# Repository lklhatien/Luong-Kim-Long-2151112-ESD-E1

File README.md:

# Luong-Kim-Long-2151112-ESD-E1

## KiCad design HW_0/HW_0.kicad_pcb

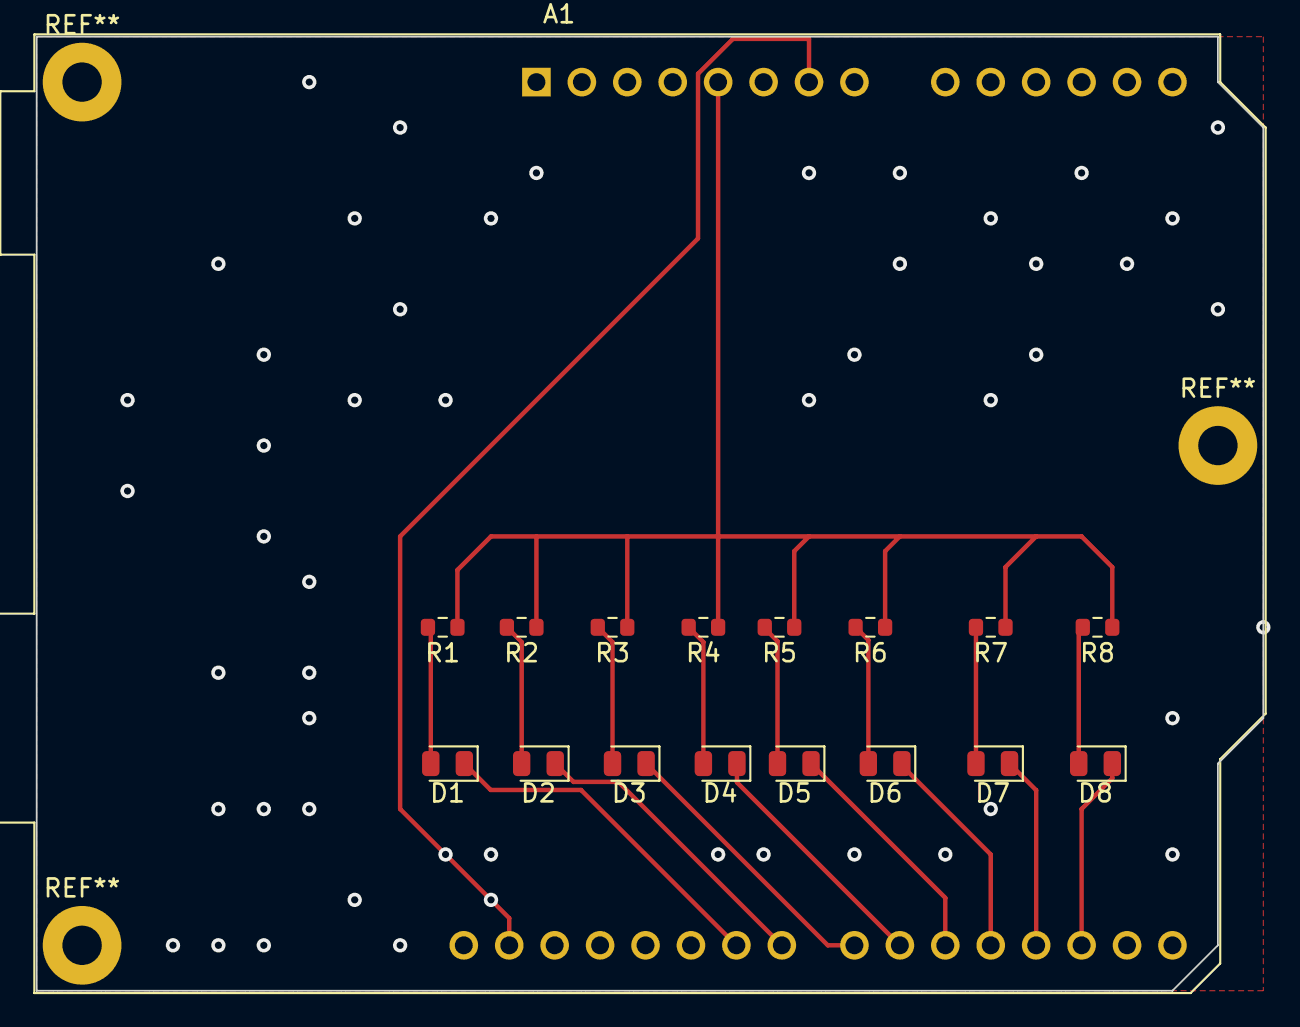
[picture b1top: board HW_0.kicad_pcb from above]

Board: 2 copper layers, 68.6 x 53.3 mm, 17 parts (0 on the bottom side), 18 nets.

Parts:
A1: Arduino_UNO_R2
D1, D2, D3, D4, D5, D6, D7, D8: LED; LED_0805_2012Metric
R1, R2, R3, R4, R5, R6, R7, R8: 247; R_0603_1608Metric

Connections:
unnamed: A1.5 (+5V), R1.1, R2.1, R3.1, R4.1, R5.1, R6.1, R7.1, R8.1
unnamed: A1.17 (D2), D8.1 (K)
unnamed: A1.18 (D3), D7.1 (K)
unnamed: A1.19 (D4), D6.1 (K)
unnamed: A1.20 (D5), D5.1 (K)
unnamed: A1.21 (D6), D4.1 (K)
unnamed: A1.22 (D7), D3.1 (K)
unnamed: A1.23 (D8), D2.1 (K)
unnamed: A1.24 (D9), D1.1 (K)
unnamed: A1.7 (GND), A1.29 (GND)
unnamed: D1.2 (A), R1.2
unnamed: D2.2 (A), R2.2
unnamed: D3.2 (A), R3.2
unnamed: D4.2 (A), R4.2
unnamed: D5.2 (A), R5.2
unnamed: D6.2 (A), R6.2
unnamed: D7.2 (A), R7.2
unnamed: D8.2 (A), R8.2
